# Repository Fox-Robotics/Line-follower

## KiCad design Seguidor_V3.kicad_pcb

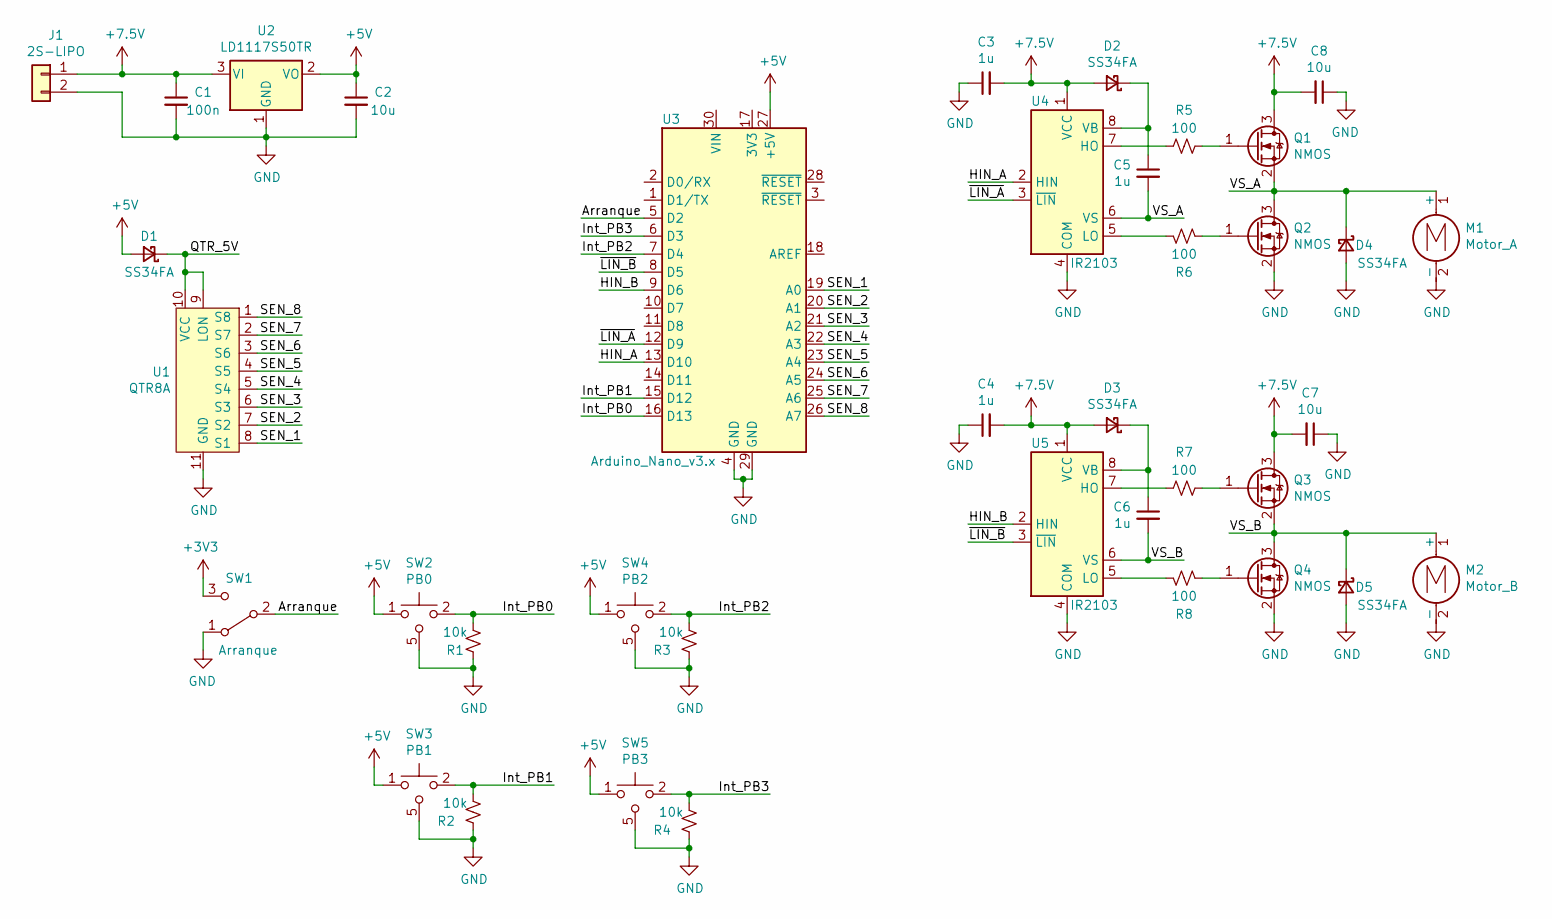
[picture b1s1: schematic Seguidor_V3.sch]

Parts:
C1: 100n; C_0805_2012Metric_Pad1.18x1.45mm_HandSolder
C2, C7, C8: 10u; C_0805_2012Metric_Pad1.18x1.45mm_HandSolder
C3, C4, C5, C6: 1u; C_0805_2012Metric_Pad1.18x1.45mm_HandSolder
D1, D2, D3, D4, D5: SS34FA; SODFL
J1: 2S-LIPO; PinHeader_1x02_P2.54mm_Vertical
M1: Motor_A; PinHeader_1x02_P2.54mm_Vertical
M2: Motor_B; PinHeader_1x02_P2.54mm_Vertical
Q1, Q2, Q3, Q4: NMOS; SOT-23; PARTNO PMV88ENER
R1, R2, R3, R4: 10k; R_0805_2012Metric_Pad1.20x1.40mm_HandSolder
R5, R6, R7, R8: 100; R_0805_2012Metric_Pad1.20x1.40mm_HandSolder
SW1: Arranque; OS102011MA1QN1
SW2: PB0; PTS526SMG20SMTR21LFS; Mouser Part Number 611-PTS526SMG20S21LF
SW3: PB1; PTS526SMG20SMTR21LFS; Mouser Part Number 611-PTS526SMG20S21LF
SW4: PB2; PTS526SMG20SMTR21LFS; Mouser Part Number 611-PTS526SMG20S21LF
SW5: PB3; PTS526SMG20SMTR21LFS; Mouser Part Number 611-PTS526SMG20S21LF
U1: QTR8A; PinHeader_1x11_P2.54mm_Vertical
U2: LD1117S50TR; SOT-223-3_TabPin2
U3: Arduino_Nano_v3.x; Arduino_Nano
U4, U5: IR2103; SOIC-8_3.9x4.9mm_P1.27mm

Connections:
+3V3: SW1.3 (C)
+5V: C2.1, D1.2 (A), SW2.1, SW2.3 (1), SW3.1, SW3.3 (1), SW4.1, SW4.3 (1), SW5.1, SW5.3 (1), U2.2 (VO), U3.27 (+5V)
+7.5V: C1.1, C3.2, C4.2, C7.2, C8.2, D2.2 (A), D3.2 (A), J1.1, Q1.3 (D), Q3.3 (D), U2.3 (VI), U4.1 (VCC), U5.1 (VCC)
/Arranque: SW1.2 (B), U3.5 (D2)
/HIN_A: U3.13 (D10), U4.2 (HIN)
/HIN_B: U3.9 (D6), U5.2 (HIN)
/Int_PB0: R1.1, SW2.2, SW2.4 (2), U3.16 (D13)
/Int_PB1: R2.1, SW3.2, SW3.4 (2), U3.15 (D12)
/Int_PB2: R3.1, SW4.2, SW4.4 (2), U3.7 (D4)
/Int_PB3: R4.1, SW5.2, SW5.4 (2), U3.6 (D3)
/QTR_5V: D1.1 (K), U1.9 (LON), U1.10 (VCC)
/SEN_1: U1.8 (S1), U3.19 (A0)
/SEN_2: U1.7 (S2), U3.20 (A1)
/SEN_3: U1.6 (S3), U3.21 (A2)
/SEN_4: U1.5 (S4), U3.22 (A3)
/SEN_5: U1.4 (S5), U3.23 (A4)
/SEN_6: U1.3 (S6), U3.24 (A5)
/SEN_7: U1.2 (S7), U3.25 (A6)
/SEN_8: U1.1 (S8), U3.26 (A7)
/VS_A: C5.2, D4.1 (K), M1.1 (+), Q1.2 (S), Q2.3 (D), U4.6 (VS)
/VS_B: C6.2, D5.1 (K), M2.1 (+), Q3.2 (S), Q4.3 (D), U5.6 (VS)
/~LIN_A: U3.12 (D9), U4.3 (~LIN)
/~LIN_B: U3.8 (D5), U5.3 (~LIN)
GND: C1.2, C2.2, C3.1, C4.1, C7.1, C8.1, D4.2 (A), D5.2 (A), J1.2, M1.2 (-), M2.2 (-), Q2.2 (S), Q4.2 (S), R1.2, R2.2, R3.2, R4.2, SW1.1 (A), SW2.5, SW2.6, SW3.5, SW3.6, SW4.5, SW4.6, SW5.5, SW5.6, U1.11 (GND), U2.1 (GND), U3.4 (GND), U3.29 (GND), U4.4 (COM), U5.4 (COM)
unnamed: C5.1, D2.1 (K), U4.8 (VB)
unnamed: C6.1, D3.1 (K), U5.8 (VB)
unnamed: Q1.1 (G), R5.1
unnamed: Q2.1 (G), R6.1
unnamed: Q3.1 (G), R7.1
unnamed: Q4.1 (G), R8.1
unnamed: R5.2, U4.7 (HO)
unnamed: R6.2, U4.5 (LO)
unnamed: R7.2, U5.7 (HO)
unnamed: R8.2, U5.5 (LO)

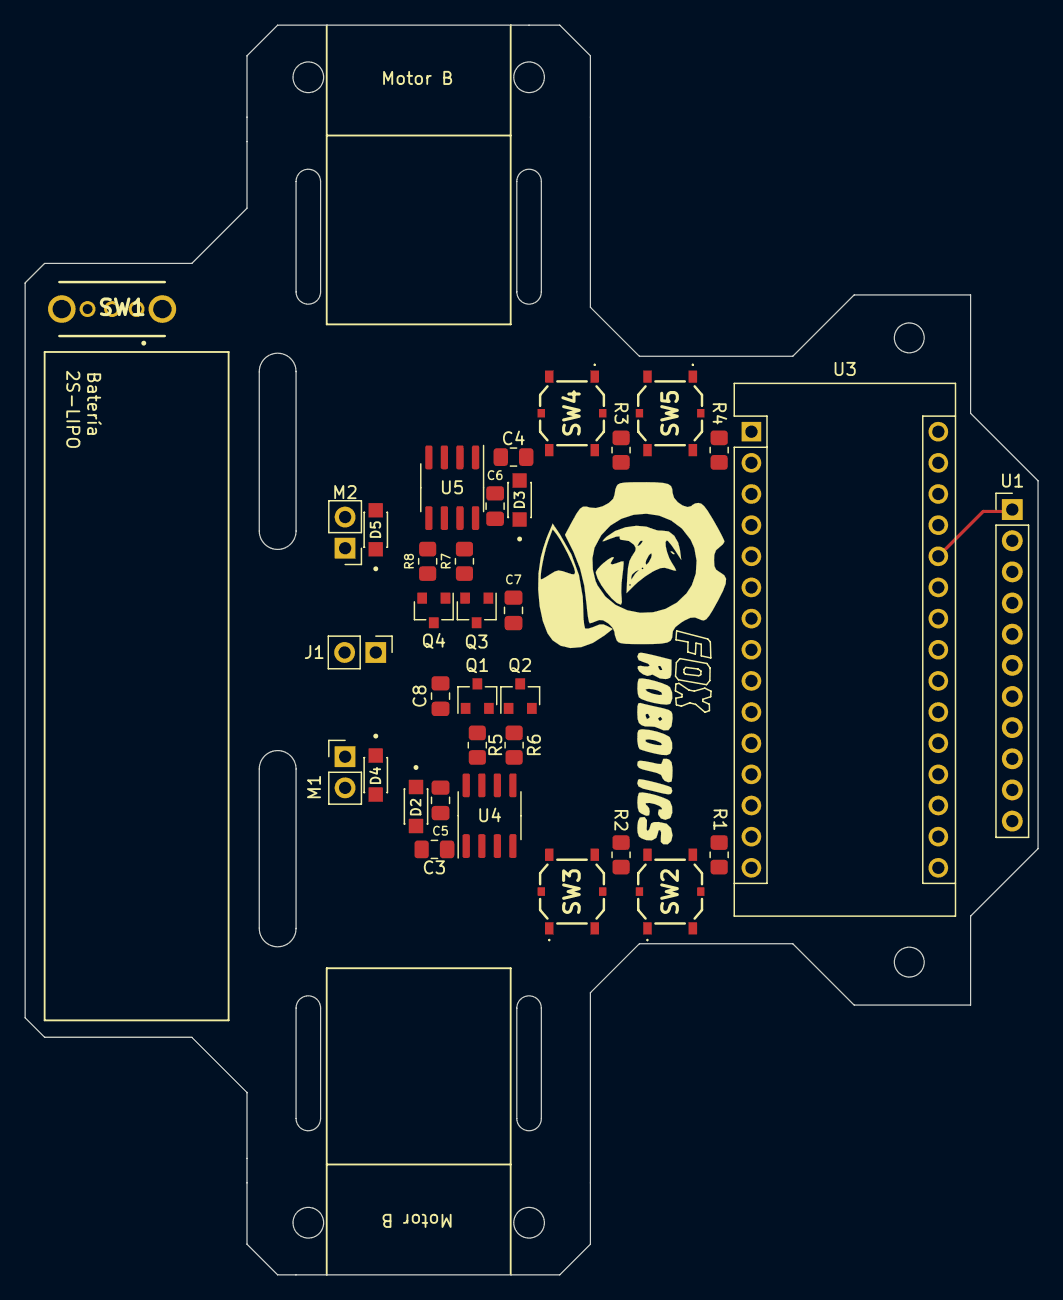
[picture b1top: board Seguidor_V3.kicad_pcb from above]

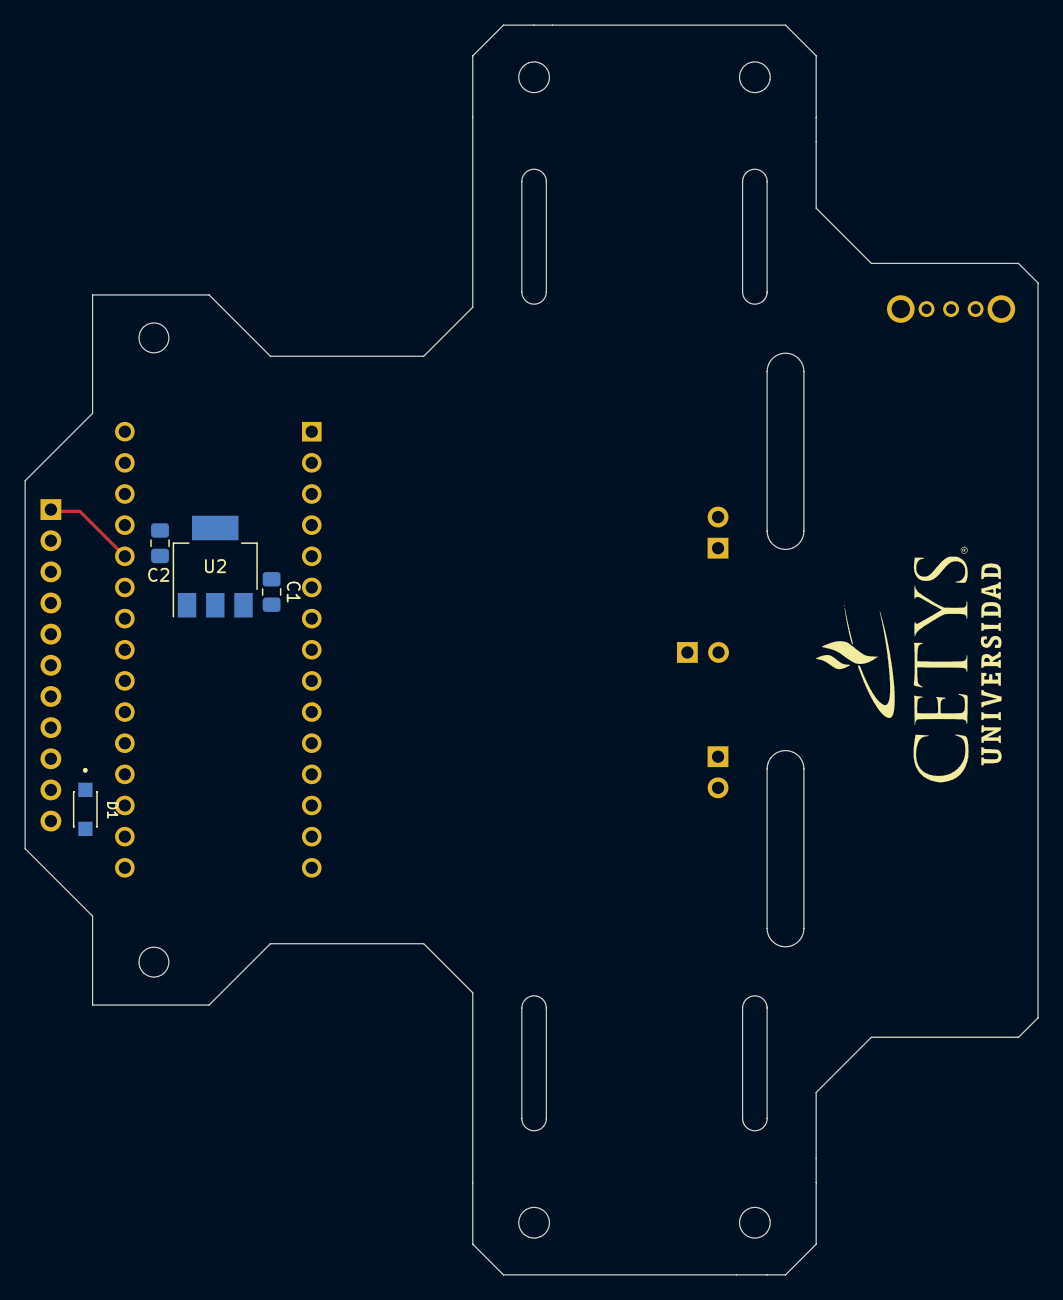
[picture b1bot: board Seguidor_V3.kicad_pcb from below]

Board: 2 copper layers, 82.6 x 101.9 mm, 38 parts (4 on the bottom side), 33 nets.

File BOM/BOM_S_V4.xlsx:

| Id | Designator | Package | Quantity | Designation | Supplier and ref
 | 3 | D1,D2,D3,D4,D5 | SODFL | 5 | SS34FA
 | 4 | C1 | C_0805_2012Metric_Pad1.18x1.45mm_HandSolder | 1 | 100n
 | 5 | C2,C7,C8 | C_0805_2012Metric_Pad1.18x1.45mm_HandSolder | 3 | 10u
 | 6 | C3,C4,C5,C6 | C_0805_2012Metric_Pad1.18x1.45mm_HandSolder | 4 | 1u
 | 9 | R1,R2,R3,R4 | R_0805_2012Metric_Pad1.20x1.40mm_HandSolder | 4 | 10k
 | 10 | R5,R6,R7,R8 | R_0805_2012Metric_Pad1.20x1.40mm_HandSolder | 4 | 100
 | 11 | SW1 | OS102011MA1QN1 | 1 | Arranque
 | 12 | SW2 | PTS526SMG20SMTR21LFS | 1 | PB0
 | 13 | SW3 | PTS526SMG20SMTR21LFS | 1 | PB1
 | 14 | U2 | SOT-223-3_TabPin2 | 1 | LD1117S50TR
 | 15 | U4,U5 | SOIC-8_3.9x4.9mm_P1.27mm | 2 | IR2103
 | 16 | Q1,Q2,Q3,Q4 | SOT-23 | 4 | PMV88ENE
 | 18 | SW4 | PTS526SMG20SMTR21LFS | 1 | PB2
 | 19 | SW5 | PTS526SMG20SMTR21LFS | 1 | PB3
 | 20 | U3 | Arduino_Nano | 1 | Arduino_Nano_v3.x
 | 21 | U1 | PinHeader_1x11_P2.54mm_Vertical | 1 | QTR8A

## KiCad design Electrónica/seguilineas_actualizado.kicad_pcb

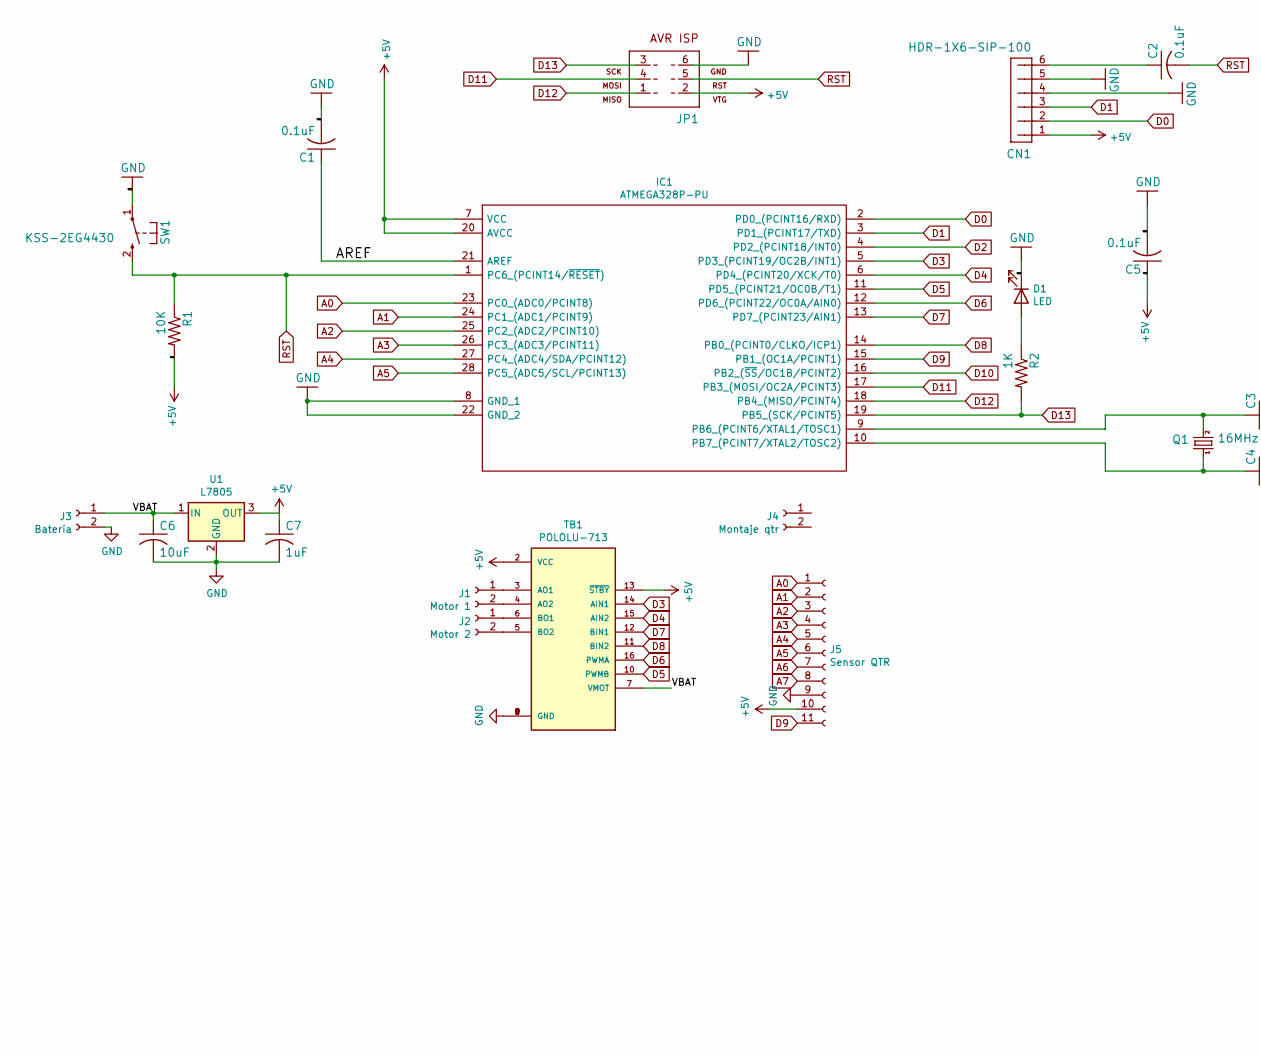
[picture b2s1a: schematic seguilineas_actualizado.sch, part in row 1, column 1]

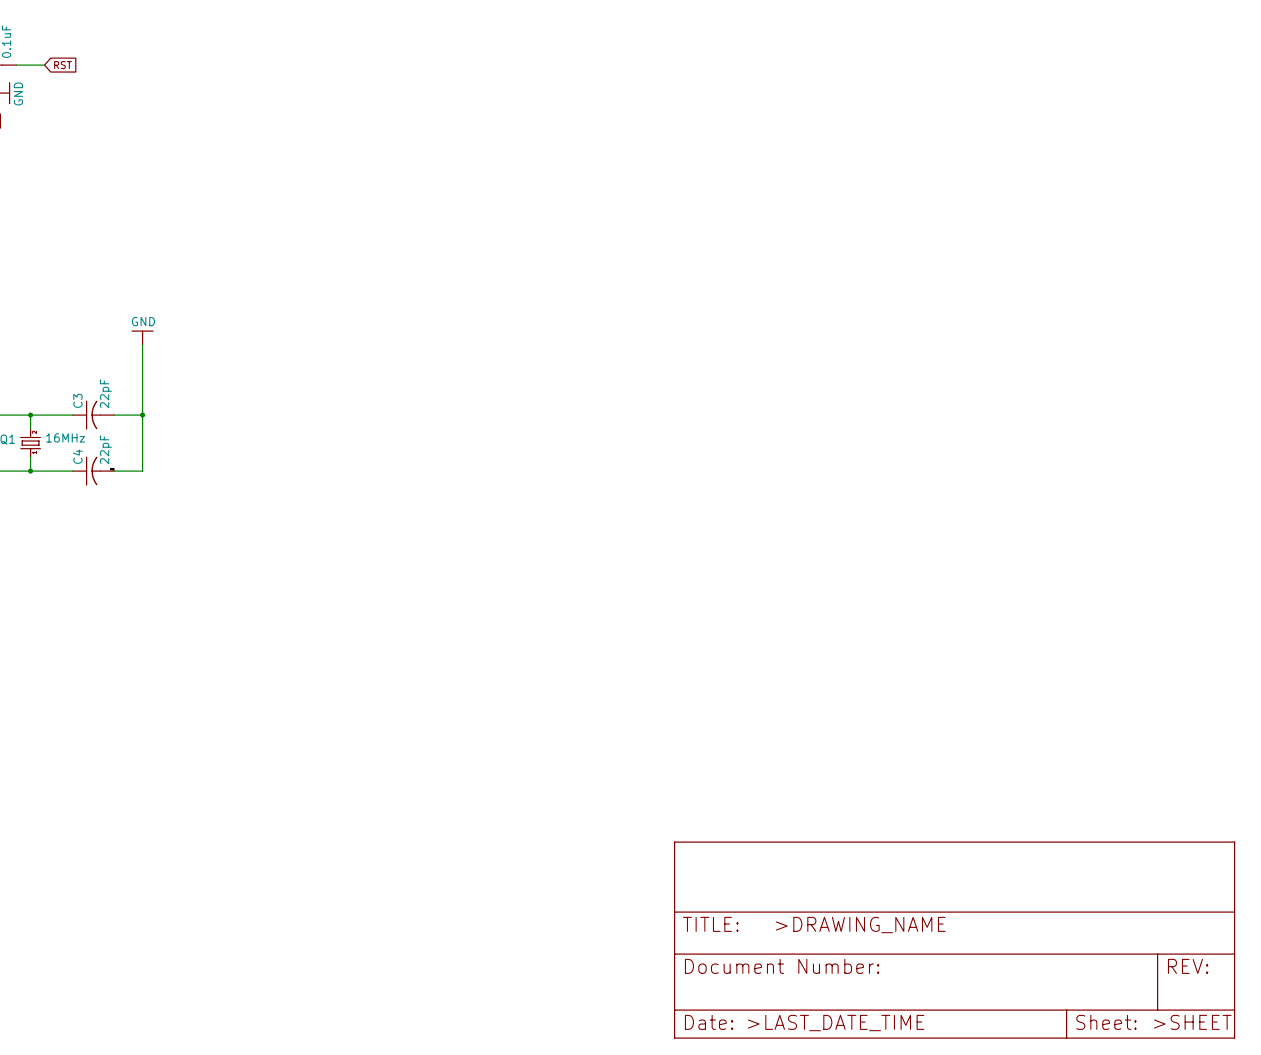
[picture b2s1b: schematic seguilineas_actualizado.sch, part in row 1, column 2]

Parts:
C1, C2, C5: 0.1uF; C_0805_2012Metric
C3, C4: 22pF; C_0805_2012Metric
C6: 10uF; C_0805_2012Metric
C7: 1uF; C_0805_2012Metric
CN1: HDR-1X6-SIP-100; PinHeader_1x06_P2.54mm_Vertical
D1: LED; LED_0805_2012Metric_Pad1.15x1.40mm_HandSolder
IC1: ATMEGA328P-PU; DIP794W46P254L2967H457Q28B; Manufacturer_Part_Number ATMEGA328P-PU; Mouser Part Number 556-ATMEGA328P-PU
J1: Motor 1; PinSocket_1x02_P2.54mm_Vertical
J2: Motor 2; PinSocket_1x02_P2.54mm_Vertical
J3: Batería; PinSocket_1x02_P2.54mm_Vertical
J4: Montaje qtr; QTR8A_Drill
J5: Sensor QTR; PinSocket_1x11_P2.54mm_Vertical
JP1: AVR-ISP-6; PinHeader_2x03_P2.54mm_Vertical
Q1: 16MHz; ABLS-16.000MHZ-B2-T
R1: 10K; R_0805_2012Metric_Pad1.20x1.40mm_HandSolder
R2: 1K; R_0805_2012Metric_Pad1.20x1.40mm_HandSolder
SW1: KSS-2EG4430; Switch ADTSM32RVTR
TB1: POLOLU-713; SHIELD_POLOLU-713
U1: L7805; LM7805

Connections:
+5V: C5.1, C7.1, CN1.1, IC1.7 (VCC), IC1.20 (AVCC), J5.10, JP1.2, R1.2, TB1.2 (VCC), TB1.13 (~STBY), U1.3 (OUT)
/AREF: C1.1, IC1.21 (AREF)
/VBAT: C6.1, J3.1, TB1.7 (VMOT), U1.1 (IN)
A0: IC1.23 (PC0_(ADC0/PCINT8)), J5.1
A1: IC1.24 (PC1_(ADC1/PCINT9)), J5.2
A2: IC1.25 (PC2_(ADC2/PCINT10)), J5.3
A3: IC1.26 (PC3_(ADC3/PCINT11)), J5.4
A4: IC1.27 (PC4_(ADC4/SDA/PCINT12)), J5.5
A5: IC1.28 (PC5_(ADC5/SCL/PCINT13)), J5.6
A6: J5.7
A7: J5.8
D0: CN1.2, IC1.2 (PD0_(PCINT16/RXD))
D1: CN1.3, IC1.3 (PD1_(PCINT17/TXD))
D2: IC1.4 (PD2_(PCINT18/INT0))
D3: IC1.5 (PD3_(PCINT19/OC2B/INT1)), TB1.14 (AIN1)
D4: IC1.6 (PD4_(PCINT20/XCK/T0)), TB1.15 (AIN2)
D5: IC1.11 (PD5_(PCINT21/OC0B/T1)), TB1.10 (PWMB)
D6: IC1.12 (PD6_(PCINT22/OC0A/AIN0)), TB1.16 (PWMA)
D7: IC1.13 (PD7_(PCINT23/AIN1)), TB1.12 (BIN1)
D8: IC1.14 (PB0_(PCINT0/CLKO/ICP1)), TB1.11 (BIN2)
D9: IC1.15 (PB1_(OC1A/PCINT1)), J5.11
D10: IC1.16 (PB2_(~SS~/OC1B/PCINT2))
D11: IC1.17 (PB3_(MOSI/OC2A/PCINT3)), JP1.4
D12: IC1.18 (PB4_(MISO/PCINT4)), JP1.1
D13: IC1.19 (PB5_(SCK/PCINT5)), JP1.3, R2.2
GND: C1.2, C3.2, C4.2, C5.2, C6.2, C7.2, CN1.4, CN1.5, D1.1 (K), IC1.8 (GND_1), IC1.22 (GND_2), J3.2, J5.9, JP1.6, SW1.1, TB1.1 (GND), TB1.8 (GND), TB1.9 (GND), U1.2 (GND)
unnamed: C2.1, CN1.6
unnamed: C3.1, IC1.9 (PB6_(PCINT6/XTAL1/TOSC1)), Q1.2
unnamed: C4.1, IC1.10 (PB7_(PCINT7/XTAL2/TOSC2)), Q1.1
unnamed: D1.2 (A), R2.1
unnamed: J1.1, TB1.3 (AO1)
unnamed: J1.2, TB1.4 (AO2)
unnamed: J2.1, TB1.6 (BO1)
unnamed: J2.2, TB1.5 (BO2)
RST: C2.2, IC1.1 (PC6_(PCINT14/~RESET)), JP1.5, R1.1, SW1.2 (S)

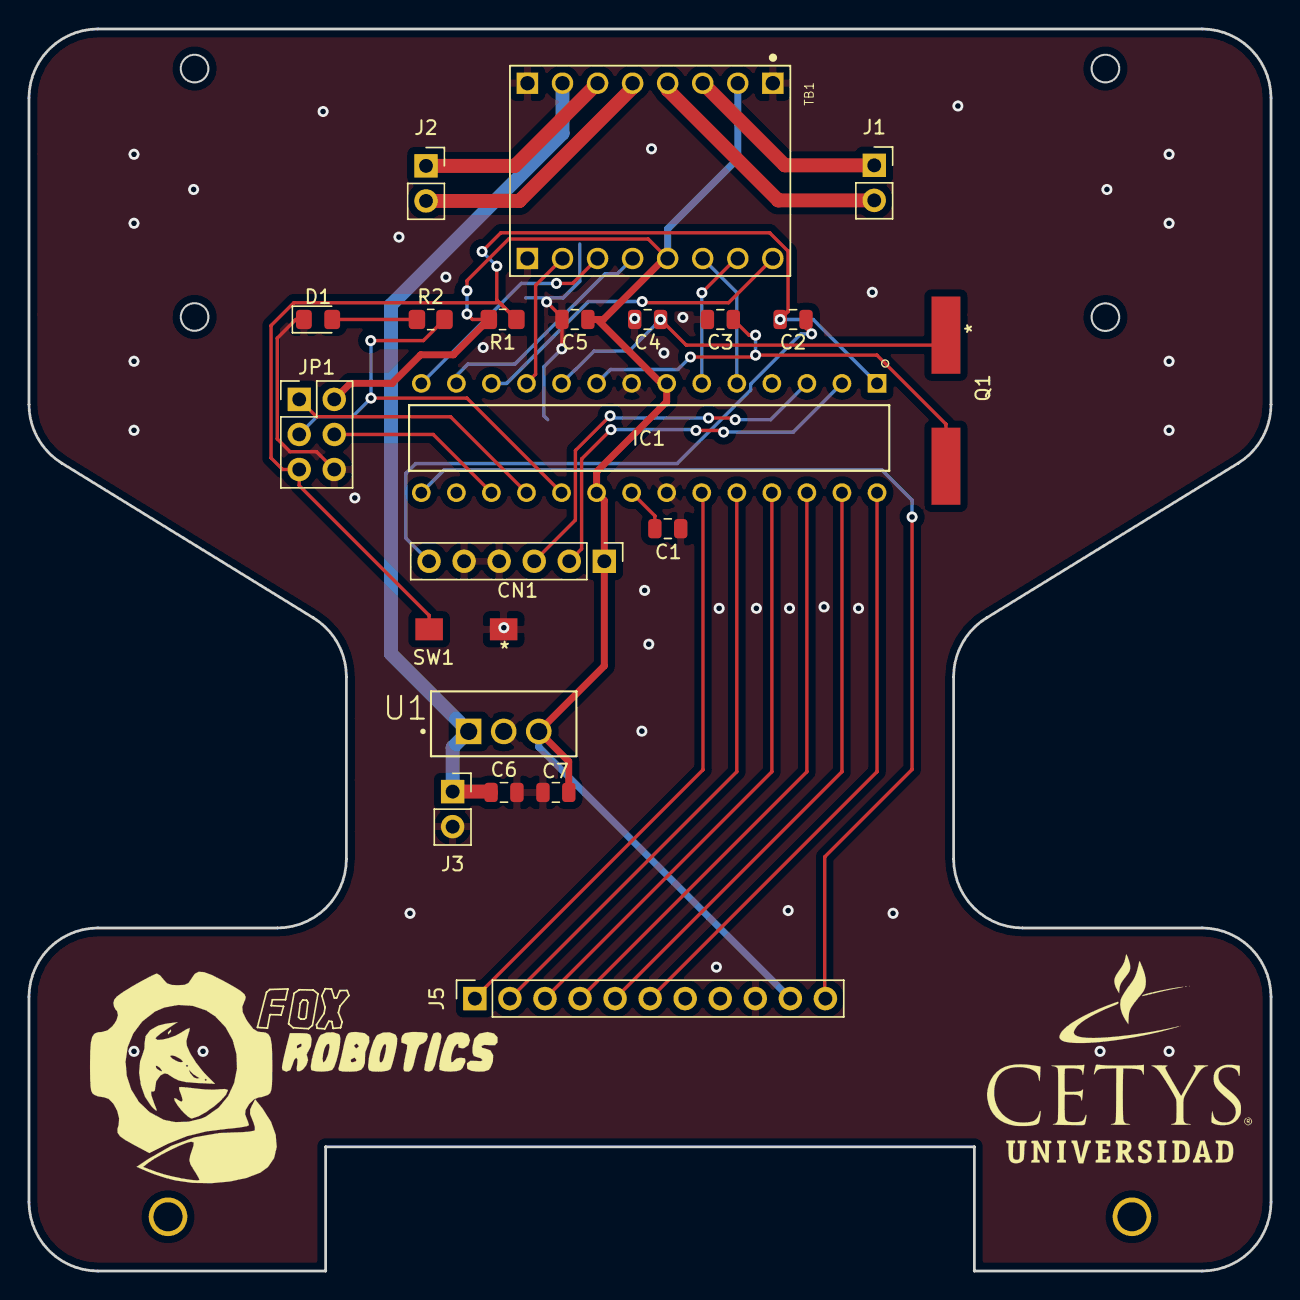
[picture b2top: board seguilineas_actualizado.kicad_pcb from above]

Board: 2 copper layers, 90.0 x 90.0 mm, 22 parts (1 on the bottom side), 31 nets.

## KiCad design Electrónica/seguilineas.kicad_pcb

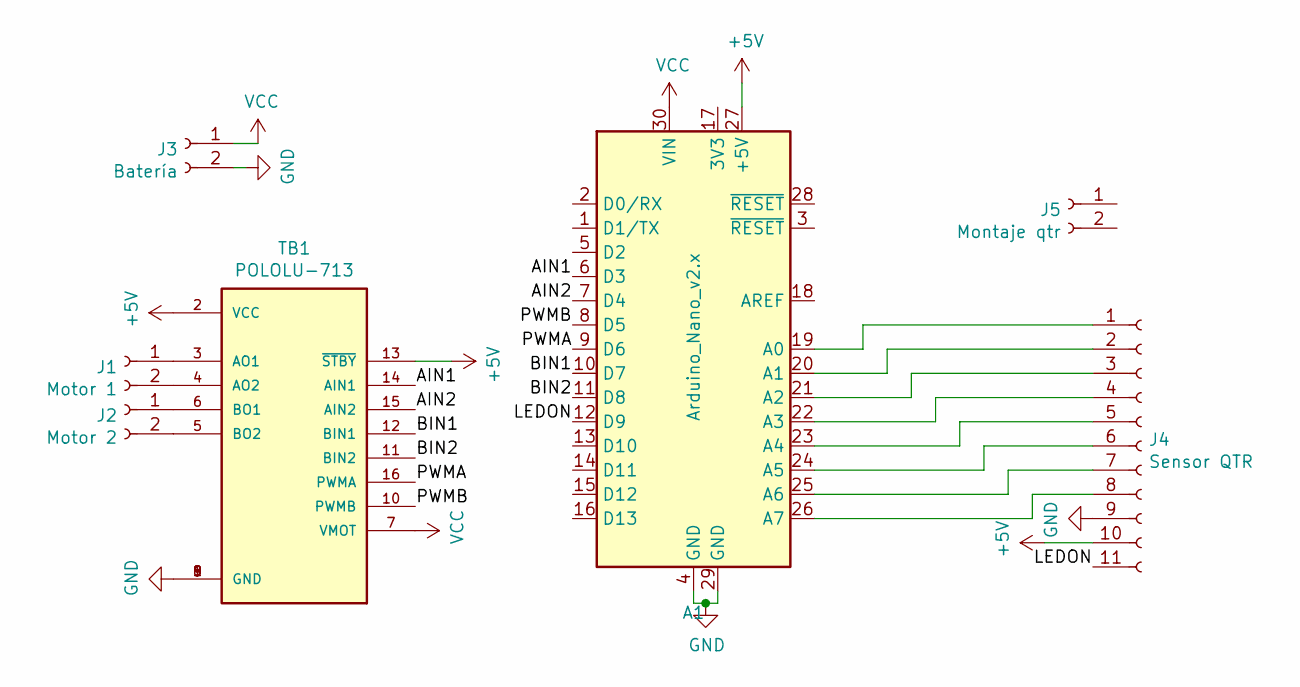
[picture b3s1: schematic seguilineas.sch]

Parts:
A1: Arduino_Nano_v2.x; NANO_33_Socket_Castell
J1: Motor 1; PinSocket_1x02_P2.00mm_Vertical
J2: Motor 2; PinSocket_1x02_P2.00mm_Vertical
J3: Batería; PinSocket_1x02_P2.00mm_Vertical
J4: Sensor QTR; PinSocket_1x11_P2.54mm_Vertical
J5: Montaje qtr; QTR8A_Drill
TB1: POLOLU-713; SHIELD_POLOLU-713

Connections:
+5V: A1.27 (+5V), J4.10, TB1.2 (VCC), TB1.13 (~STBY)
/AIN1: A1.6 (D3), TB1.14 (AIN1)
/AIN2: A1.7 (D4), TB1.15 (AIN2)
/BIN1: A1.10 (D7), TB1.12 (BIN1)
/BIN2: A1.11 (D8), TB1.11 (BIN2)
/LEDON: A1.12 (D9), J4.11
/PWMA: A1.9 (D6), TB1.16 (PWMA)
/PWMB: A1.8 (D5), TB1.10 (PWMB)
GND: A1.4 (GND), A1.29 (GND), J3.2, J4.9, TB1.1 (GND), TB1.8 (GND), TB1.9 (GND)
unnamed: A1.19 (A0), J4.1
unnamed: A1.20 (A1), J4.2
unnamed: A1.21 (A2), J4.3
unnamed: A1.22 (A3), J4.4
unnamed: A1.23 (A4), J4.5
unnamed: A1.24 (A5), J4.6
unnamed: A1.25 (A6), J4.7
unnamed: A1.26 (A7), J4.8
unnamed: J1.1, TB1.3 (AO1)
unnamed: J1.2, TB1.4 (AO2)
unnamed: J2.1, TB1.6 (BO1)
unnamed: J2.2, TB1.5 (BO2)
VCC: A1.30 (VIN), J3.1, TB1.7 (VMOT)

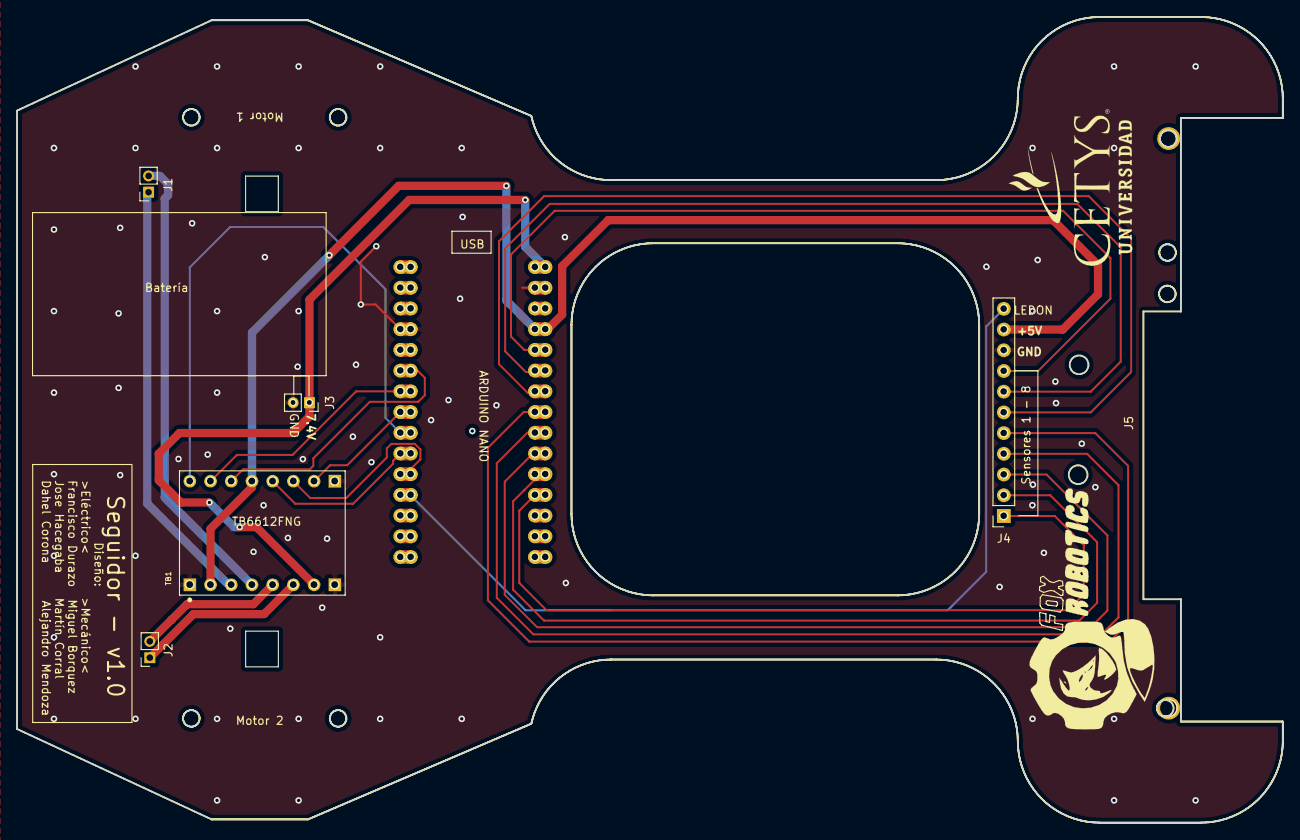
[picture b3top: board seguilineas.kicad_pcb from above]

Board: 2 copper layers, 155.2 x 98.8 mm, 7 parts (0 on the bottom side), 22 nets.
